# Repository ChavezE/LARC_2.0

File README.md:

# LARC_2.0

This repository contains the approach used by RoBorregos Team in the Latin American Robotics Competition 2017.
RoBorregos is the international representative robotics team of Tecnologico de Monterrey, Campus Monterrey. It
obtained second place in the LARC 2016, hosted by IEEE on Recife, Brasil.

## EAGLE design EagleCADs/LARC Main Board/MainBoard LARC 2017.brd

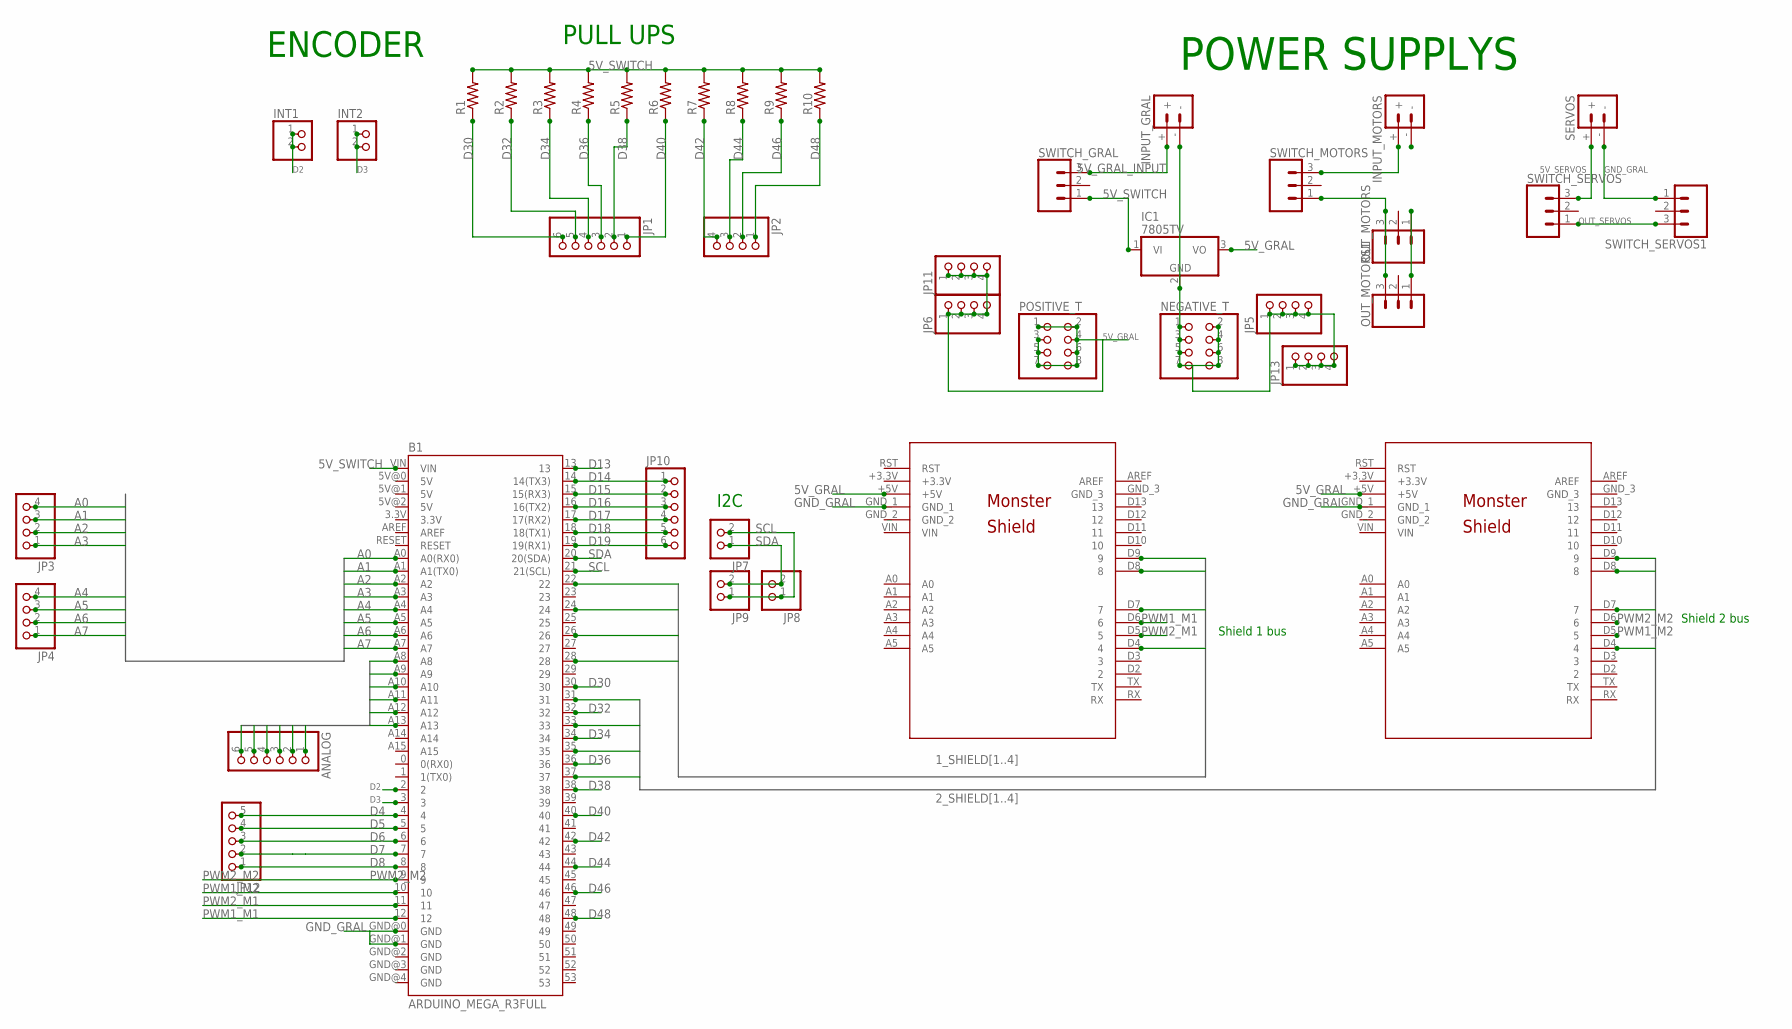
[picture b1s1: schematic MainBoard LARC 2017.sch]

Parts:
ANALOG: PINHD-1X6; 1X06
B1: ARDUINO_MEGA_R3FULL; ARDUINO_MEGA
IC1: 7805TV; TO220V
INPUT_GRAL: BATTERY_CONN_DEANS; DEANS
INPUT_MOTORS: BATTERY_CONN_DEANS; DEANS
INT1, INT2: PINHD-1X2; 1X02
JP1, JP10: PINHD-1X6; 1X06
JP2, JP3, JP4, JP5, JP6, JP11, JP13: PINHD-1X4; 1X04
JP7, JP8, JP9: PINHD-1X2; 1X02
JP12: PINHD-1X5; 1X05
MS_1, MS_2: MONSTER_SHIELD
NEGATIVE_T: PINHD-2X4; 2X04
OUT_MOTORS, OUT_MOTORS1: CONN_03LONGPADS; 1X03_LONGPADS
POSITIVE_T: PINHD-2X4; 2X04
R1, R2, R3, R4, R5, R6, R7, R8, R9, R10: R-US_0207/9; 0207/9
SERVOS: BATTERY_CONN_DEANS; DEANS
SWITCH_GRAL: CONN_03LONGPADS; 1X03_LONGPADS
SWITCH_MOTORS: CONN_03LONGPADS; 1X03_LONGPADS
SWITCH_SERVOS, SWITCH_SERVOS1: CONN_03LONGPADS; 1X03_LONGPADS

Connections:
1_SHIELD1: B1.28, MS_1.D4 (4)
1_SHIELD2: B1.26, MS_1.D7 (7)
1_SHIELD3: B1.24, MS_1.D8 (8)
1_SHIELD4: B1.22, MS_1.D9 (9)
2_SHIELD1: B1.31, MS_2.D4 (4)
2_SHIELD2: B1.33, MS_2.D7 (7)
2_SHIELD3: B1.35, MS_2.D8 (8)
2_SHIELD4: B1.37, MS_2.D9 (9)
5V_GRAL: IC1.3 (VO), JP6.1, JP6.2, JP6.3, JP6.4, JP11.1, JP11.2, JP11.3, JP11.4, MS_1.+5V, MS_2.+5V, POSITIVE_T.1, POSITIVE_T.2, POSITIVE_T.3, POSITIVE_T.4, POSITIVE_T.5, POSITIVE_T.6, POSITIVE_T.7, POSITIVE_T.8
5V_GRAL_INPUT: INPUT_GRAL.+, SWITCH_GRAL.3
5V_SERVOS: SERVOS.+, SWITCH_SERVOS.3
5V_SWITCH: B1.VIN, IC1.1 (VI), R1.2, R2.2, R3.2, R4.2, R5.2, R6.2, R7.2, R8.2, R9.2, R10.2, SWITCH_GRAL.1
A0: B1.A0 (A0(RX0)), JP3.4
A1: B1.A1 (A1(TX0)), JP3.3
A2: B1.A2, JP3.2
A3: B1.A3, JP3.1
A4: B1.A4, JP4.4
A5: B1.A5, JP4.3
A6: B1.A6, JP4.2
A7: B1.A7, JP4.1
ANALOGS8: ANALOG.6, B1.A8
ANALOGS9: ANALOG.5, B1.A9
ANALOGS10: ANALOG.4, B1.A10
ANALOGS11: ANALOG.3, B1.A11
ANALOGS12: ANALOG.2, B1.A12
ANALOGS13: ANALOG.1, B1.A13
D2: B1.2, INT1.1, INT1.2
D3: B1.3, INT2.1, INT2.2
D4: B1.4, JP12.5
D5: B1.5, JP12.4
D6: B1.6, JP12.3
D7: B1.7, JP12.2
D8: B1.8, JP12.1
D13: B1.13
D14: B1.14 (14(TX3)), JP10.1
D15: B1.15 (15(RX3)), JP10.2
D16: B1.16 (16(TX2)), JP10.3
D17: B1.17 (17(RX2)), JP10.4
D18: B1.18 (18(TX1)), JP10.5
D19: B1.19 (19(RX1)), JP10.6
D30: B1.30, JP1.6, R1.1
D32: B1.32, JP1.5, R2.1
D34: B1.34, JP1.4, R3.1
D36: B1.36, JP1.3, R4.1
D38: B1.38, JP1.2, R5.1
D40: B1.40, JP1.1, R6.1
D42: B1.42, JP2.4, R7.1
D44: B1.44, JP2.3, R8.1
D46: B1.46, JP2.2, R9.1
D48: B1.48, JP2.1, R10.1
GND_GRAL: B1.GND@0 (GND), B1.GND@1 (GND), IC1.2 (GND), INPUT_GRAL.-, INPUT_MOTORS.-, JP5.1, JP5.2, JP5.3, JP5.4, JP13.1, JP13.2, JP13.3, JP13.4, MS_1.GND_1, MS_2.GND_1, NEGATIVE_T.1, NEGATIVE_T.2, NEGATIVE_T.3, NEGATIVE_T.4, NEGATIVE_T.5, NEGATIVE_T.6, NEGATIVE_T.7, NEGATIVE_T.8, OUT_MOTORS.1, OUT_MOTORS1.1, SERVOS.-, SWITCH_SERVOS1.1
unnamed: INPUT_MOTORS.+, SWITCH_MOTORS.3
unnamed: OUT_MOTORS.3, OUT_MOTORS1.3, SWITCH_MOTORS.1
OUT_SERVOS: SWITCH_SERVOS.1, SWITCH_SERVOS1.3
PWM1_M1: B1.12, MS_1.D6 (6)
PWM1_M2: B1.10, MS_2.D5 (5)
PWM2_M1: B1.11, MS_1.D5 (5)
PWM2_M2: B1.9, MS_2.D6 (6)
SCL: B1.21 (21(SCL)), JP7.2, JP8.1, JP9.1
SDA: B1.20 (20(SDA)), JP7.1, JP8.2, JP9.2

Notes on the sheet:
Shield 1 bus
Shield 2 bus
POWER SUPPLYS
ENCODER
PULL UPS
I2C

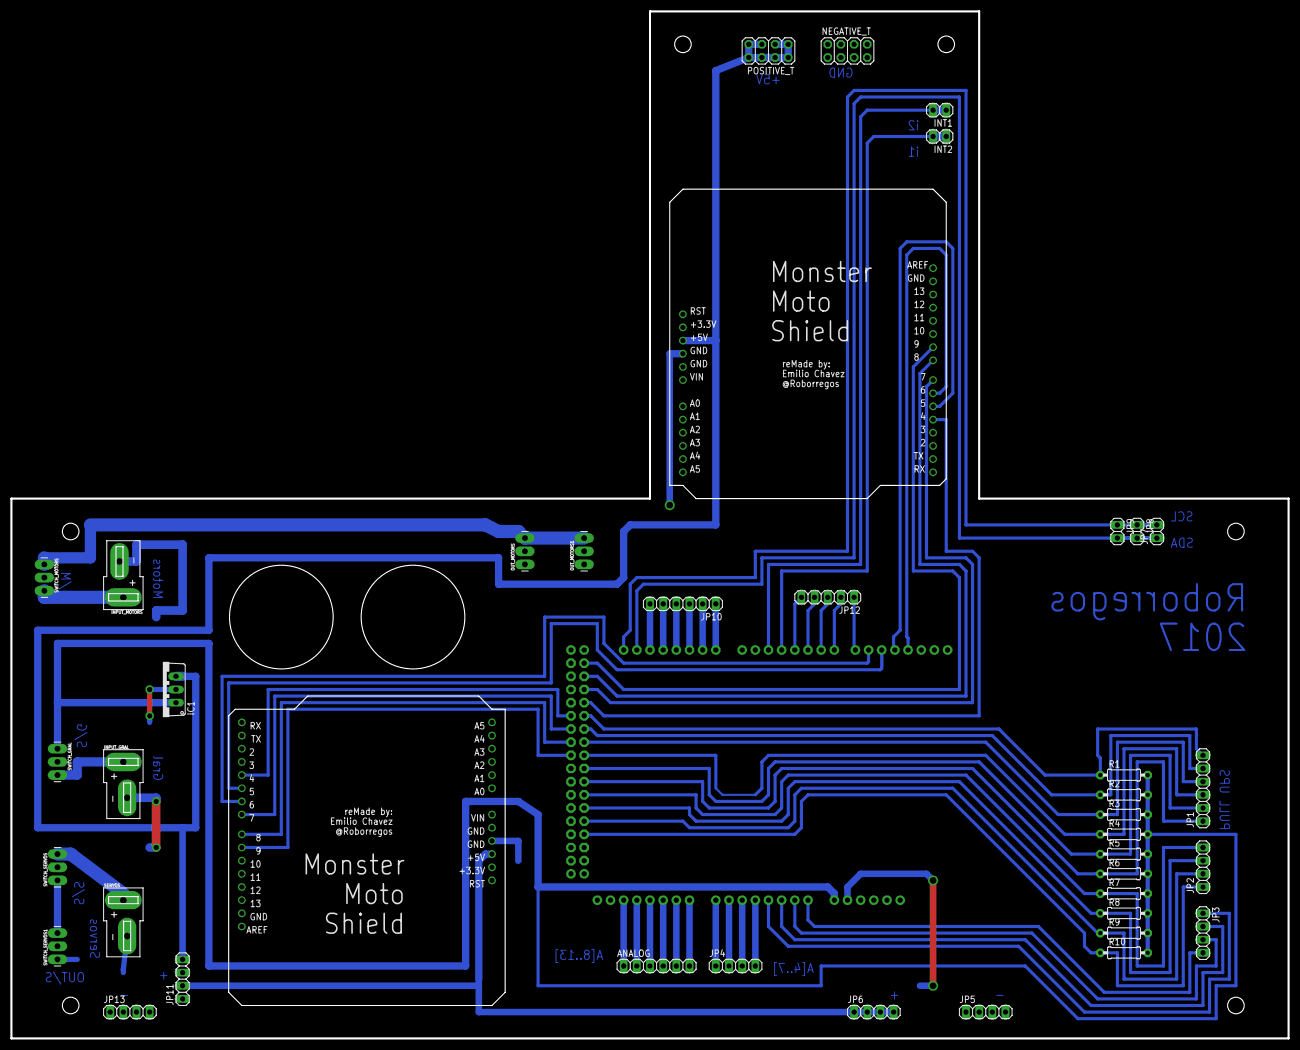
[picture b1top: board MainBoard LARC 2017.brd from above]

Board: 2 copper layers, 246.4 x 198.1 mm, 41 parts (1 on the bottom side), 59 nets.

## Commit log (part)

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2016-12-24 photos
2017-01-04 Comments in 'makeTissue' function
    This function was created during september 2016 and was used to create a
    tissue of squares that represent the cow that we are looking for. Maybe
    it could be substituted with a more efficient algorithm that has been
    already developed.
2017-03-26 Adding MachineL
    new approaches
2017-03-26 exmple
2017-03-28 Getting started
    Ordering floders, adding new contributions
2017-03-28 Naming folders
    adding proper names, creating working folders
2017-03-28 ejemplo
    Cardozo
2017-03-28 Funcion adelante1
    Primera prueba de adelante, con los pines de motores y P
2017-03-29 Funcionario Movimientos
    Programa version 1 con las funciones básicas de movimientos
2017-03-29 funciones hasta terrines
2017-03-29 functions for serial
2017-03-29 aef
    asdsgdg
2017-03-29 Archivos de vision
    qwerty
2017-03-29 Aplicando vision
    bla bla bla
2017-03-29 Arreglando detalles
    bla bla bla
2017-03-30 Change in sintaxys
2017-03-30 Main for TMR2017
2017-03-30 Calibracion hecha con vacas
2017-03-30 Funcionario perfecto y Vasos en progreso
    Funcionario basico ya con la funciones excelentisimas con constantes de
    TMR. Funcion agarrar vaso en proceso, falta revision.
2017-03-31 vasos
2017-04-07 Actualizado los archivos
    Las últimas versiones de todos los codigos ya estan, tambien borrado lo
    viejo que no se usaba
2017-05-29 colectivo good ideas
    previo merge entre funciones
2017-05-29 Creating algorithm tester
2017-05-30 more stuff to clean
    rompiendo funciones obsoletas
2017-05-30 Ordering libs
2017-05-30 get squares update
    Lib version update and is there a cow update
2017-06-01 extension de fotos
    cambiando .JPG a .jpg
2017-06-01 Get Good Sqrs pruebas de tiempo en raspberry
2017-06-01 Deleting previous lib
2017-06-02 Prueba envio inf
2017-06-02 Archivos Prueba para comunicacion serial
2017-06-02 Intento Serial
2017-06-02 All functions, still not checked
2017-06-03 Added comments on functions
2017-06-03 Added lcd functions
2017-06-03 Changed some data using byte wise
2017-06-03 Del sleeps
2017-06-04 Del delays and added sharp communication
2017-06-04 Moved files
2017-06-04 correction of variables
2017-06-05 Modified communication and organize arduino functions
2017-06-06 Arrangements
2017-06-06 Addded calibration file
2017-06-06 Added calibration file
2017-06-06 turns functions
2017-06-06 Calibration
2017-06-07 Cleaning branches
2017-06-08 Basic functions
2017-06-08 Update communication and switch case
2017-06-09 solved conflict
2017-06-09 Adding libraries
2017-06-09 Sensor master library
2017-06-09 We are moving
2017-06-09 Movements from rasp
2017-06-09 time to build a miracle
2017-06-09 improving view, setting up cow slope
2017-06-09 one level tissue
2017-06-11 showing level
2017-06-11 setting up bash program to drive the rasp
2017-06-11 modifiying navegation
2017-06-14 calibrating
2017-06-20 depth photos
2017-06-20 depth optimization
2017-06-23 more depth photos
2017-06-24 GetInCow function added
2017-06-25 Just some tests with the tissue
2017-06-26 more test with depth
2017-06-26 Fixed error about validations
2017-06-27 solving dir problems
2017-06-27 boton
2017-06-30 sharp com
2017-06-30 Communication test
2017-07-02 addition of cow2.xml for tests
2017-07-03 About to test center allignment
2017-07-03 Buttons
2017-07-03 Added grab terrines function
2017-07-04 included new cow pictures
2017-07-04 Solved case error
2017-07-04 Addition of cascade training for new cow
2017-07-04 Adition of calibration program for turns
2017-07-04 Calibrated for turns
2017-07-04 Get in Cow added
2017-07-04 last
2017-07-04 cleanning
2017-07-05 Changed testing movements and fixed some errors
2017-07-05 Fixed global error
2017-07-05 succes with structure
2017-07-05 ordering photos
2017-07-05 New funtions for turns
2017-07-05 Calibration success
2017-07-05 Added milking function
2017-07-05 Function for alignment
2017-07-11 Campus Party results
2017-07-27 Fixed small error
2017-07-27 Added script for cropping images
2017-07-27 updating mainRasp
2017-07-28 Changes constants
2017-07-29 Walking detecting version 2
2017-08-02 getInCow mejorado
2017-08-02 acomodo de case
2017-08-02 getInCow
2017-08-02 adding test photos
2017-08-03 cases ordered
2017-08-03 Added turn direction
2017-08-03 fixing mortal bugs,adding distance calibration
2017-08-03 Solved identation error
2017-08-03 fixing walking detecting
2017-08-03 adding distance
2017-08-03 fix distance
2017-08-03 correcting A and B
2017-08-04 control Robot with keyboard
2017-08-04 Paralelism refined
2017-08-04 Smooth movments
2017-08-04 Fixed sintaxys error
2017-08-04 Adding EagleCAD files
2017-08-04 webcam and control robot on thread are now working
2017-08-07 PCB Lower level finished
2017-08-07 Parallelism ready
2017-08-09 Triangle refined
2017-08-09 Correction to walking detecting
2017-08-09 Correction on PCB main board
2017-08-10 working on triangle
2017-08-20 Adding TDP to the repository
2017-08-29 aproach for distance
2017-08-30 fixing folder path
2017-08-30 emptying prev frames on calb
2017-08-30 bug fix
2017-09-09 MainBoard v1.0
2017-09-09 white and black images
2017-09-09 new milker
2017-09-09 finding tank and centering
2017-09-09 distance calib
2017-09-10 Confirm if theres a cow and allign
2017-09-10 Lets see if this works
2017-09-11 triangle updated
2017-09-17 going back a little
2017-09-17 first Complete function of goToStart
2017-09-19 Aproach Ready
2017-09-20 Added 3 new libraries: Estadisticas, Logger and QuickSort
2017-09-20 Changed getDistance(sharp) to use Estadisticas.h (QuickSort)
2017-09-20 Added a round to getCompass()
2017-09-22 Added python files for Rasp to receive logs from Arduino
2017-09-22 Modified and added two new functions from platform functions
2017-09-22 Turning angle depends on the detected angle
2017-09-24 Added the new working version of goGrabTerrine
2017-09-27 pins update
2017-09-28 Added script to test the whole vision algorithm
2017-10-01 Pins limit swithces front and back
2017-10-01 Added new pins of sharps and note about velocity
2017-10-01 Pin encoder update
2017-10-01 Testing the vision
2017-10-03 Revision de funciones
2017-10-04 functions of plattform, update of pins and added new limit read in calibrations
2017-10-07 placa
2017-10-07 Corrected the P consts from forward and turn
2017-10-08 Changed encoders constant and adapted untilWallN
2017-10-11 New cascade, cowtummy2.0
2017-10-19 Changed to new values for servos
2017-10-19 Updated status of sharp pins and added sharpClaw in calibrateSharp
2017-10-20 Updated to the new sharp pins
2017-10-20 Prepared to marge with development
2017-10-20 Correction of parking function
2017-10-20 New getInCow function
2017-10-20 correction of back sharp pin
2017-10-21 solved error of variable name
2017-10-21 Added a basic goGrabTerrineBasic with its new basic methods
2017-10-21 Added the goGrabTerrineBasic to work forwarding
2017-10-23 Changed goGrabTerrineBasic to use sharp LB and updated some servos.write
2017-10-23 Replaced old communication code for grabTerrine with the new one
2017-10-24 First aproach
2017-10-25 added debugging function
2017-10-25 adding push buttons to main
2017-10-25 botones en rasp
2017-10-27 pins updates
2017-10-27 added limit calibration function
2017-10-28 added motors for milker
2017-10-28 Front sharp connected
2017-10-28 added tab for readibility
2017-10-28 Update of angles for open and close claw
2017-10-28 initial functions
2017-10-28 Added NewPing library for ultrasonic
2017-10-28 Modified some servos.write value
2017-10-28 No watchdog
2017-10-28 Setted Loggers to not print anything in Serial
2017-10-28 Moved all the libraries include to Main.ino
2017-10-28 Improved the order of pins, consts declarations in Main
2017-10-28 Removed unused control constants in Main
2017-10-28 Cleaned setup in Main and added missing pinmode of limits
2017-10-28 Added the methods headers declaration zone in Main
2017-10-28 Added the default param to clawToStartPoint
2017-10-29 conflict?
2017-10-29 Decreased minimum number of squares
2017-10-29 Implementation of terrines and vision
2017-10-29 Hot fixes for vision
2017-10-29 Calibration vision with new robot
2017-10-29 Improved HAAR detection, modified clearImage function
2017-10-30 Added missing P-effects in both wheels-sides in backwardP
2017-10-30 Fixed an error in forwardP
2017-10-30 Changed to use a temporal variable in forwardP and backwardP
2017-10-30 Changed name of constPCorrectN to constPCorrect
2017-10-30 update of milker
2017-11-01 new pins for extractor
2017-11-01 update pins for milker
2017-11-01 Milker functions of going up, down, start the extractor, stop it, etc
2017-11-02 aux Servo move faster
2017-11-02 update pinLMD pin
2017-11-02 move Milker
2017-11-02 added functions to communication, goToStart, moveMilkerUp/Down
2017-11-02 less time of going milkerUp
2017-11-02 added Funcitons to comm
2017-11-02 comment pygame function
2017-11-02 conflict solved
2017-11-02 pin update pinLO
2017-11-03 Added the new version of goToStart
2017-11-03 pin sharp funel
2017-11-03 Added checking near side wall
2017-11-03 Comment out the gate part for wait the sharp back to pass
2017-11-03 Improved cases when arriving horizontally to terrine zone thinking it was the gate
2017-11-03 El cambio mas importante de todos
2017-11-05 Improved forwardWithRightWall and added returning sharp front and back
2017-11-05 Changed forwardWithRight to backwardWithLeft
2017-11-06 Added the correction with the wall in goGrabTerrine
2017-11-06 Preparing for competition
2017-11-06 Added debugger option, eliminated all waitKeys for competition
2017-11-07 i2c communication with milker
2017-11-07 Added file with the method of leave terrine
2017-11-07 close milker function added
2017-11-07 Changed the angleObjective to param in backwardUntilNoLeft
2017-11-07 milker motor functions
2017-11-07 Fixed a missing param in a call to backwardUntilNoLeft
2017-11-07 Added function forwardWithLeftWall
2017-11-07 Fixed compilation errors in forwardUntilNoLeft
2017-11-07 Changed to use forwardWithLeftWall in leaveTerrine
2017-11-07 deleted repeated pins of milker motors Added I2C communication with milker
2017-11-07 I2C communication functions between Mega and Nano
2017-11-07 ignore I2C tryouts
2017-11-07 update distance sensor fo claw from sharp to ultrasonic
2017-11-07 more time for milker to go up
2017-11-07 Small changes in grabTerrineBasic
2017-11-07 change initial angles
2017-11-07 Changed name of formulaBackwardWithLeftWall to formulaFollowWithWall
2017-11-08 Changes made, after tests in the Arena
2017-11-08 Added working-alone version of goGrabTerrineSideLeft
2017-11-08 Removed initial turn in goGrabTerrine(right)
2017-11-08 Changed grabTerrine to use the sideRight and sideLeft version
2017-11-08 go slower to make sure the openMilker function works
2017-11-08 openDirective to get the glove out
2017-11-08 Finding tank with haar cascade
2017-11-08 This is a test only
2017-11-08 new pins for servo up/down and extractor
2017-11-08 Added some TODOs in goGrabTerrine
2017-11-08 calibrated center to tank
2017-11-08 extra
2017-11-09 Added validation for tank
2017-11-09 restar
2017-11-09 watchdog for upper part of milker
2017-11-09 Big Bug correction
2017-11-09 add restart function to communication
2017-11-09 forwardUntilWall update to get the parameter dist = 0 and goToStartRes
2017-11-09 Improved goToStart and stuff
2017-11-09 go to tank comm
2017-11-09 watchdog on moving milker down
2017-11-09 Fixed some stuff
2017-11-09 Before the first round
2017-11-09 forward and backward N encoder steps
2017-11-09 cambios restart
2017-11-09 Fixed somethings in goGrabTerrine
2017-11-09 Fixed some compilation errors and duplicated methods
2017-11-09 Added some small changes in leave and grab Terrine
2017-11-09 restart calibrated
2017-11-10 updates of restar
2017-11-10 Fixed zero-issue in grabTerrine with ultrasonic
2017-11-10 Added more cm in backwards in goToStart
2017-11-10 Fixed a probably-bug in tryToGrabTerrines
2017-11-10 clawToStartPoint
2017-11-10 Added the goGrabTerrineUltraBasic to start grabbing the terrine
2017-11-10 Fixed and improved forwardUntilNoLeft
2017-11-10 Implemented leaveTerrineRight
2017-11-10 Added when calling restart, the change of global variable inARestart
2017-11-10 Added goToStart New
2017-11-10 Fixed an error with choosing between ultraBasic and basic
2017-11-10 Fixed some little things
2017-11-11 Last day of rounds
2017-11-11 adding restart main

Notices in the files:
parts and their libraries:
SparkFun-Boards: Licensing: Creative Commons ShareAlike 4.0 International - https://creativecommons.org/licenses/by-sa/4.0
